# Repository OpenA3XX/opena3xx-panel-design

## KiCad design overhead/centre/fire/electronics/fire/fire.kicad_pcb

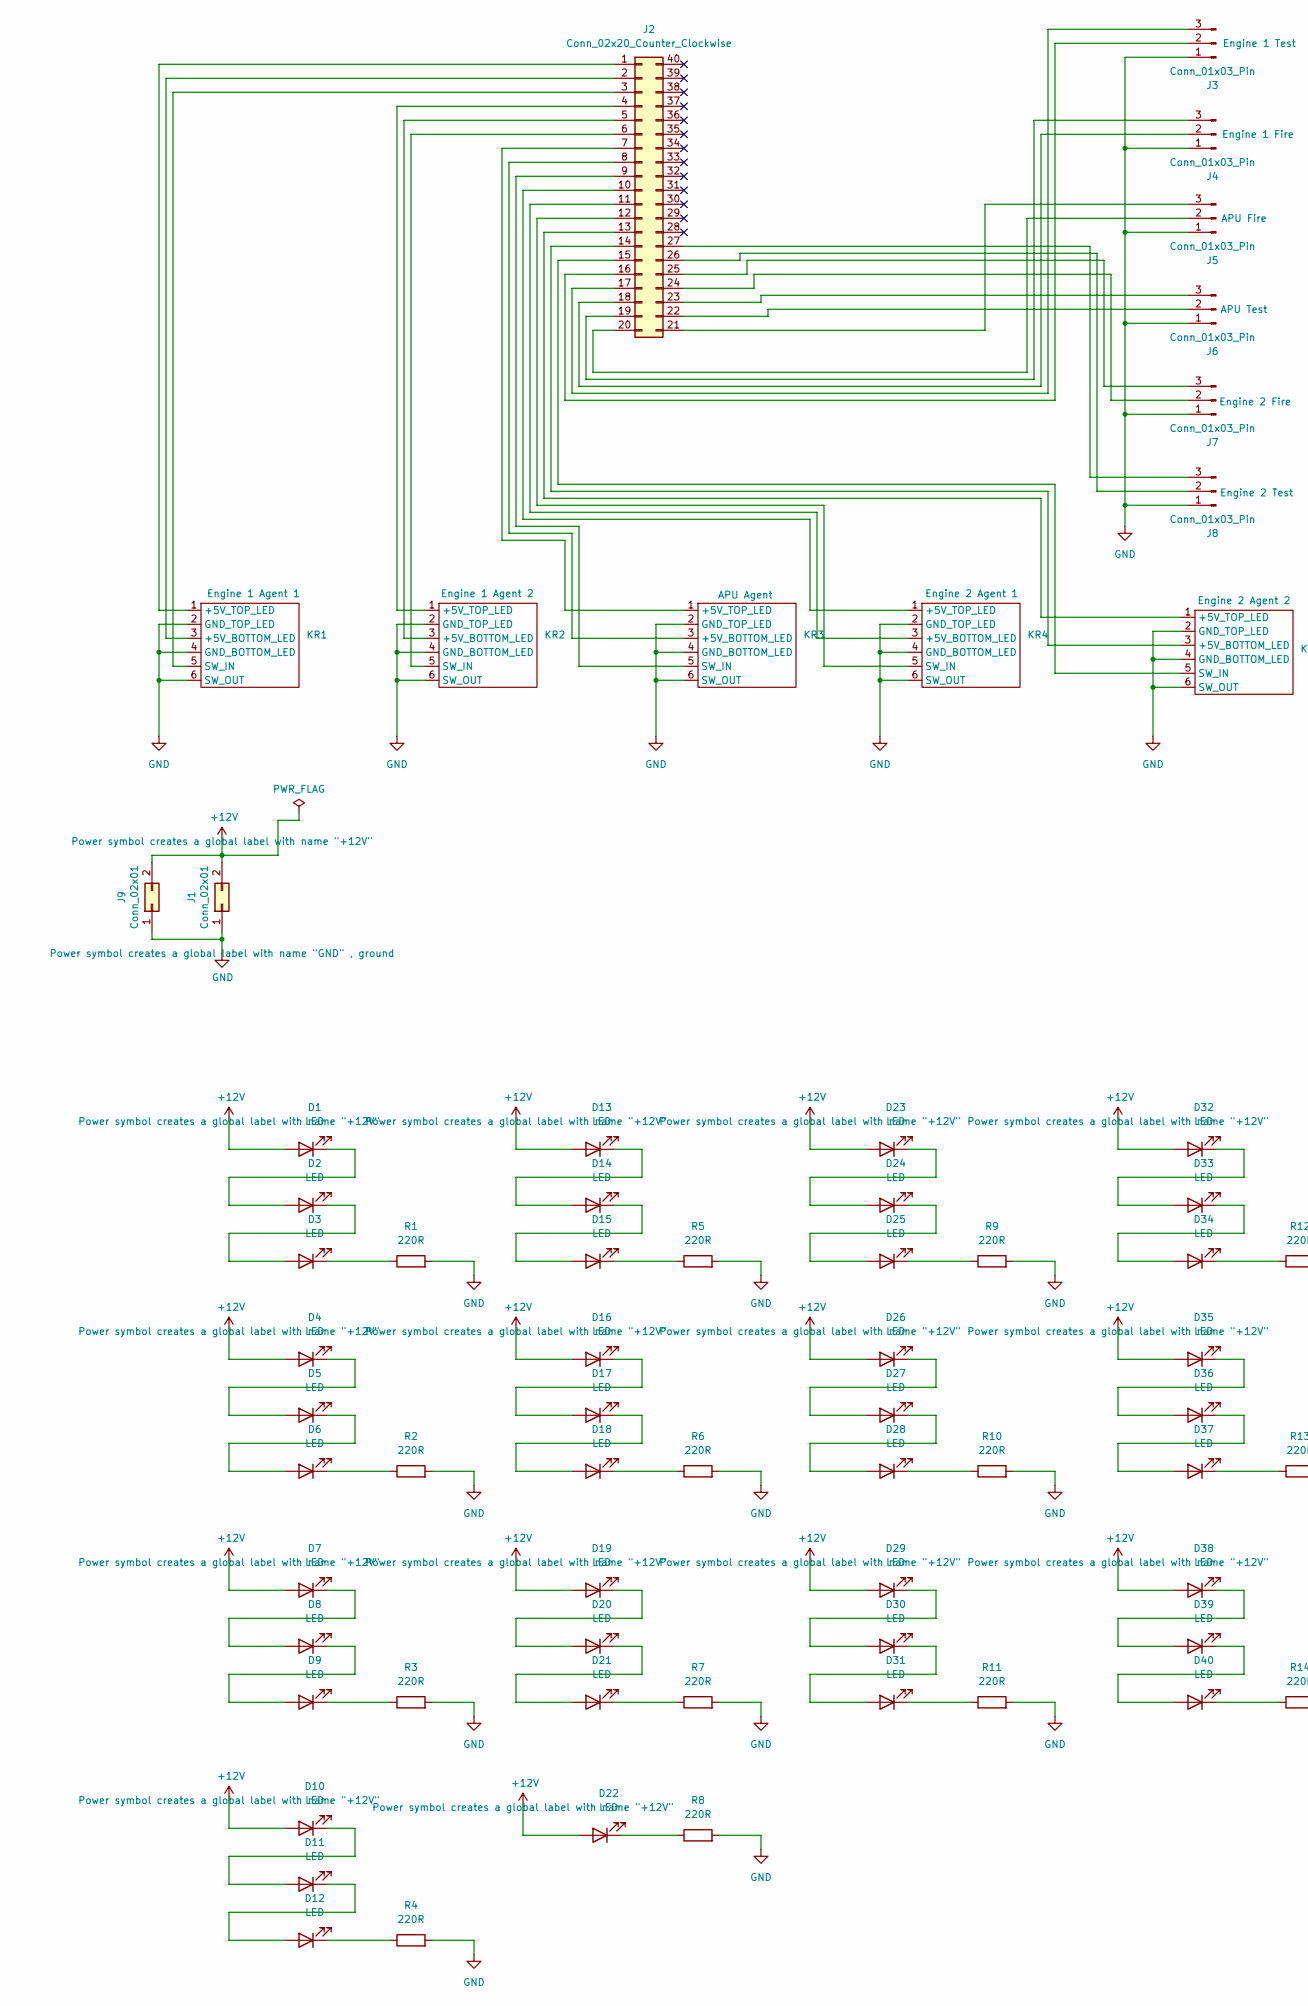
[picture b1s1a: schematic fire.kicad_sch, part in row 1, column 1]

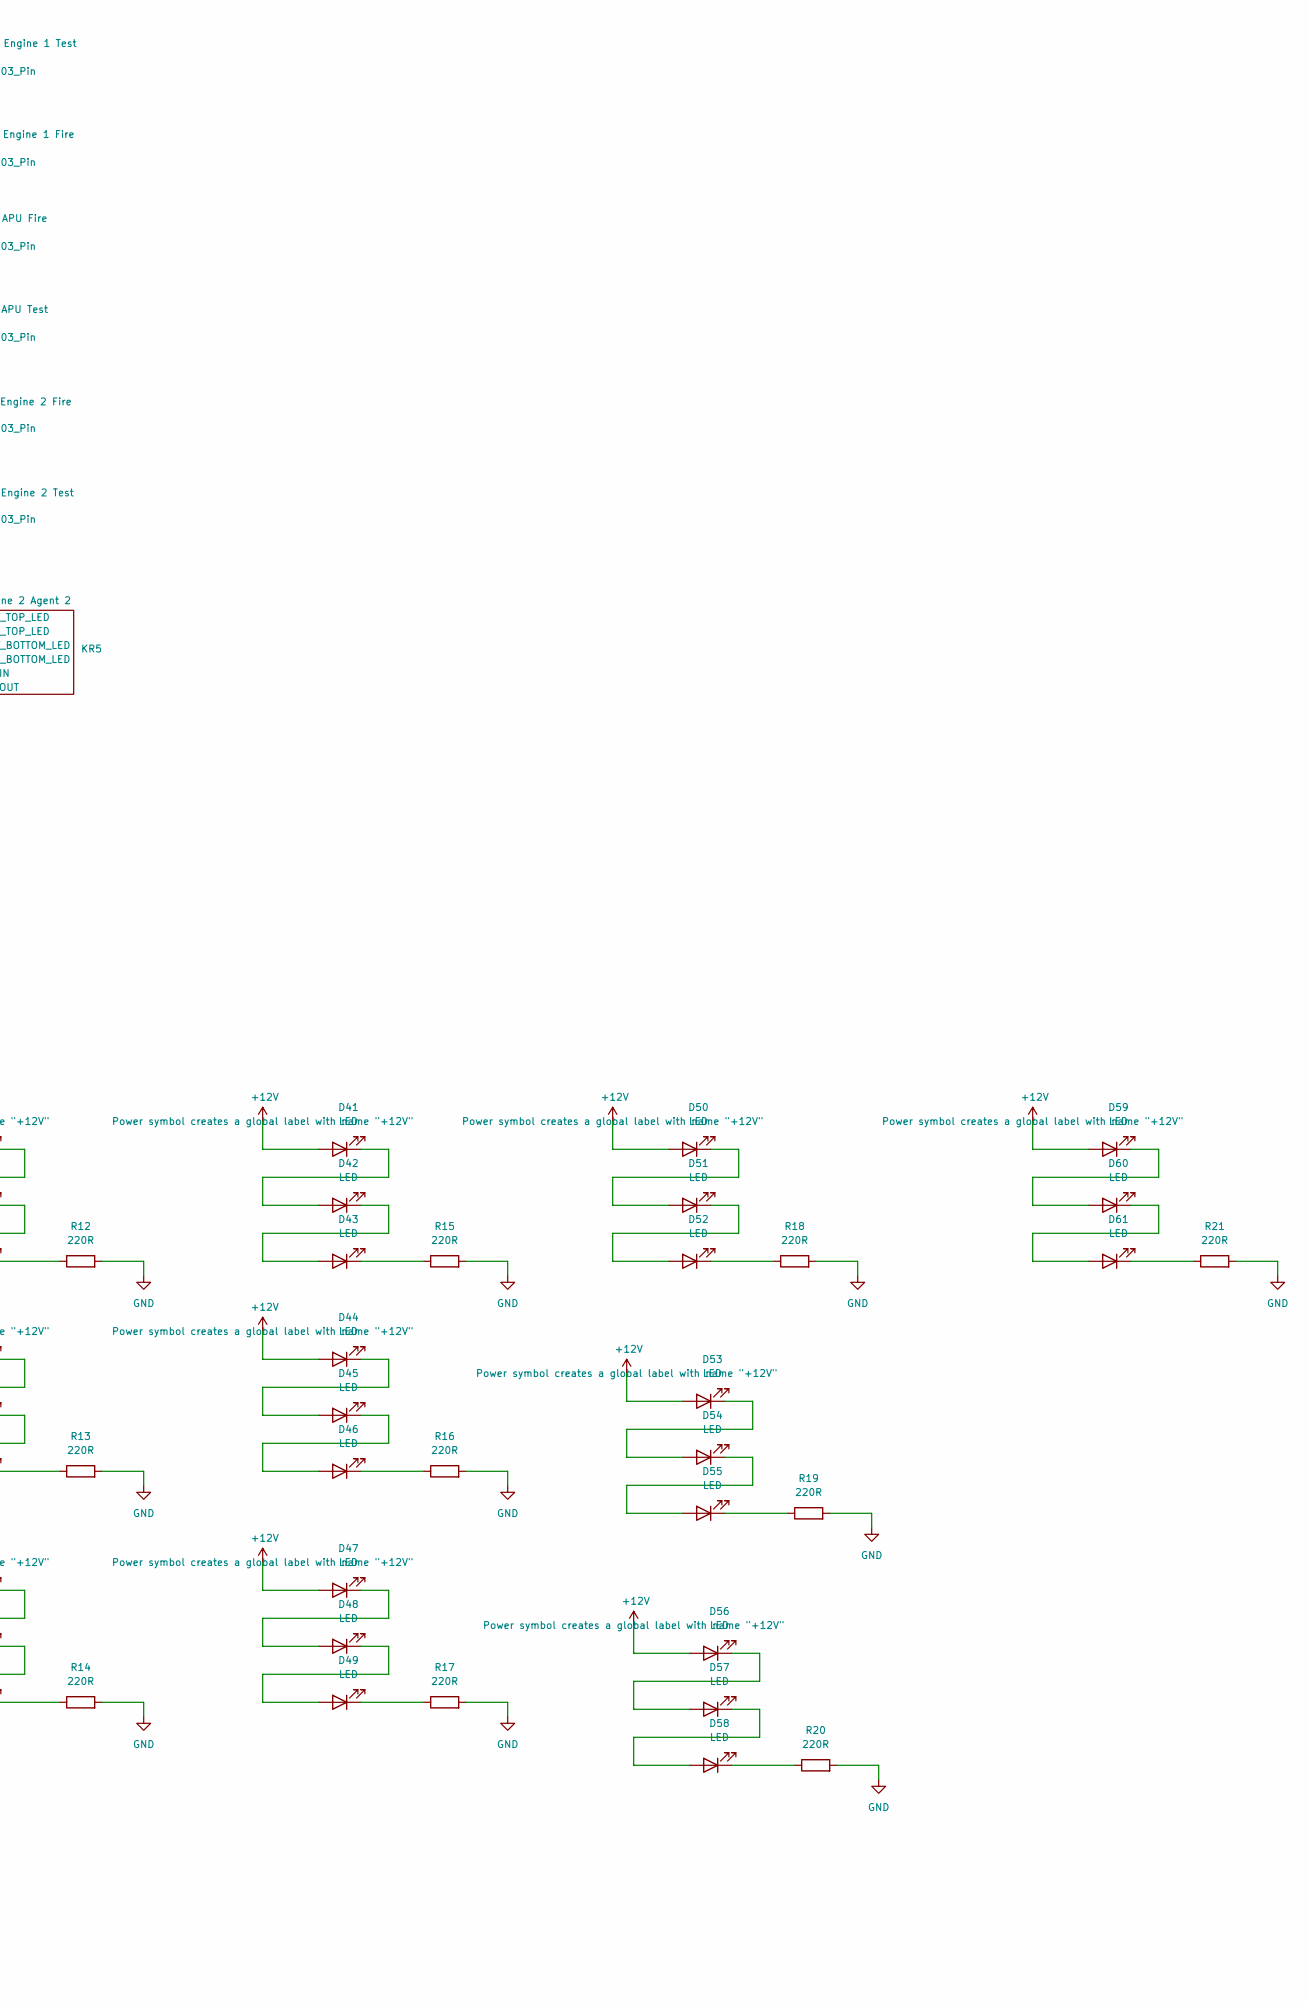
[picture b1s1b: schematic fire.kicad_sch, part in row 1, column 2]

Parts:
D1, D2, D3, D4, D5, D6, D7, D8, D9, D10, D11, D12, D13, D14, D15, D16, D17, D18, D19, D20, D21, D22, D23, D24, D25, D26, D27, D28, D29, D30, D31, D32, D33, D34, D35, D36, D37, D38, D39, D40, D41, D42, D43, D44, D45, D46, D47, D48, D49, D50, D51, D52, D53, D54, D55, D56, D57, D58, D59, D60, D61: LED; LED_Everlight-SMD3528_3.5x2.8mm_67-21ST
J1, J9: Conn_02x01; TerminalBlock_bornier-2_P5.08mm
J2: Conn_02x20_Counter_Clockwise; PinHeader_2x20_P2.54mm_Vertical
J3, J4, J5, J6, J7, J8: Conn_01x03_Pin; PinHeader_1x03_P2.54mm_Vertical
KR1, KR2, KR3, KR4, KR5: Korry Switch
R1, R2, R3, R4, R5, R6, R7, R8, R9, R10, R11, R12, R13, R14, R15, R16, R17, R18, R19, R20, R21: 220R; R_1206_3216Metric_Pad1.30x1.75mm_HandSolder

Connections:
+12V: D1.2 (A), D4.2 (A), D7.2 (A), D10.2 (A), D13.2 (A), D16.2 (A), D19.2 (A), D22.2 (A), D23.2 (A), D26.2 (A), D29.2 (A), D32.2 (A), D35.2 (A), D38.2 (A), D41.2 (A), D44.2 (A), D47.2 (A), D50.2 (A), D53.2 (A), D56.2 (A), D59.2 (A), J1.2, J9.2
GND: J1.1, J3.1, J4.1, J5.1, J6.1, J7.1, J8.1, J9.1, KR1.2 (GND_TOP_LED), KR1.4 (GND_BOTTOM_LED), KR1.6 (SW_OUT), KR2.2 (GND_TOP_LED), KR2.4 (GND_BOTTOM_LED), KR2.6 (SW_OUT), KR3.2 (GND_TOP_LED), KR3.4 (GND_BOTTOM_LED), KR3.6 (SW_OUT), KR4.2 (GND_TOP_LED), KR4.4 (GND_BOTTOM_LED), KR4.6 (SW_OUT), KR5.2 (GND_TOP_LED), KR5.4 (GND_BOTTOM_LED), KR5.6 (SW_OUT), R1.2, R2.2, R3.2, R4.2, R5.2, R6.2, R7.2, R8.2, R9.2, R10.2, R11.2, R12.2, R13.2, R14.2, R15.2, R16.2, R17.2, R18.2, R19.2, R20.2, R21.2
unnamed: D1.1 (K), D2.2 (A)
unnamed: D2.1 (K), D3.2 (A)
unnamed: D3.1 (K), R1.1
unnamed: D4.1 (K), D5.2 (A)
unnamed: D5.1 (K), D6.2 (A)
unnamed: D6.1 (K), R2.1
unnamed: D7.1 (K), D8.2 (A)
unnamed: D8.1 (K), D9.2 (A)
unnamed: D9.1 (K), R3.1
unnamed: D10.1 (K), D11.2 (A)
unnamed: D11.1 (K), D12.2 (A)
unnamed: D12.1 (K), R4.1
unnamed: D13.1 (K), D14.2 (A)
unnamed: D14.1 (K), D15.2 (A)
unnamed: D15.1 (K), R5.1
unnamed: D16.1 (K), D17.2 (A)
unnamed: D17.1 (K), D18.2 (A)
unnamed: D18.1 (K), R6.1
unnamed: D19.1 (K), D20.2 (A)
unnamed: D20.1 (K), D21.2 (A)
unnamed: D21.1 (K), R7.1
unnamed: D22.1 (K), R8.1
unnamed: D23.1 (K), D24.2 (A)
unnamed: D24.1 (K), D25.2 (A)
unnamed: D25.1 (K), R9.1
unnamed: D26.1 (K), D27.2 (A)
unnamed: D27.1 (K), D28.2 (A)
unnamed: D28.1 (K), R10.1
unnamed: D29.1 (K), D30.2 (A)
unnamed: D30.1 (K), D31.2 (A)
unnamed: D31.1 (K), R11.1
unnamed: D32.1 (K), D33.2 (A)
unnamed: D33.1 (K), D34.2 (A)
unnamed: D34.1 (K), R12.1
unnamed: D35.1 (K), D36.2 (A)
unnamed: D36.1 (K), D37.2 (A)
unnamed: D37.1 (K), R13.1
unnamed: D38.1 (K), D39.2 (A)
unnamed: D39.1 (K), D40.2 (A)
unnamed: D40.1 (K), R14.1
unnamed: D41.1 (K), D42.2 (A)
unnamed: D42.1 (K), D43.2 (A)
unnamed: D43.1 (K), R15.1
unnamed: D44.1 (K), D45.2 (A)
unnamed: D45.1 (K), D46.2 (A)
unnamed: D46.1 (K), R16.1
unnamed: D47.1 (K), D48.2 (A)
unnamed: D48.1 (K), D49.2 (A)
unnamed: D49.1 (K), R17.1
unnamed: D50.1 (K), D51.2 (A)
unnamed: D51.1 (K), D52.2 (A)
unnamed: D52.1 (K), R18.1
unnamed: D53.1 (K), D54.2 (A)
unnamed: D54.1 (K), D55.2 (A)
unnamed: D55.1 (K), R19.1
unnamed: D56.1 (K), D57.2 (A)
unnamed: D57.1 (K), D58.2 (A)
unnamed: D58.1 (K), R20.1
unnamed: D59.1 (K), D60.2 (A)
unnamed: D60.1 (K), D61.2 (A)
unnamed: D61.1 (K), R21.1
unnamed: J2.1, KR1.1 (+5V_TOP_LED)
unnamed: J2.2, KR1.3 (+5V_BOTTOM_LED)
unnamed: J2.3, KR1.5 (SW_IN)
unnamed: J2.4, KR2.1 (+5V_TOP_LED)
unnamed: J2.5, KR2.3 (+5V_BOTTOM_LED)
unnamed: J2.6, KR2.5 (SW_IN)
unnamed: J2.7, KR3.1 (+5V_TOP_LED)
unnamed: J2.8, KR3.3 (+5V_BOTTOM_LED)
unnamed: J2.9, KR3.5 (SW_IN)
unnamed: J2.10, KR4.1 (+5V_TOP_LED)
unnamed: J2.11, KR4.3 (+5V_BOTTOM_LED)
unnamed: J2.12, KR4.5 (SW_IN)
unnamed: J2.13, KR5.1 (+5V_TOP_LED)
unnamed: J2.14, KR5.3 (+5V_BOTTOM_LED)
unnamed: J2.15, KR5.5 (SW_IN)
unnamed: J2.16, J3.2
unnamed: J2.17, J3.3
unnamed: J2.18, J4.2
unnamed: J2.19, J4.3
unnamed: J2.20, J5.2
unnamed: J2.21, J5.3
unnamed: J2.22, J6.2
unnamed: J2.23, J6.3
unnamed: J2.24, J7.2
unnamed: J2.25, J7.3
unnamed: J2.26, J8.2
unnamed: J2.27, J8.3

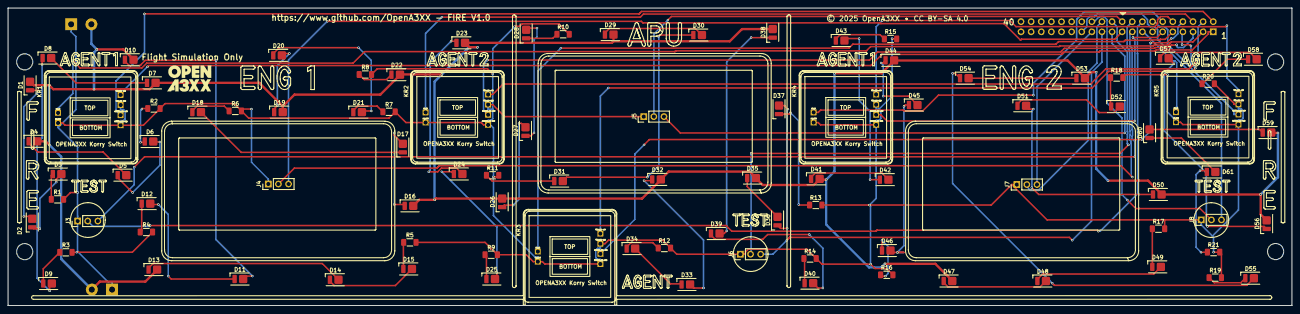
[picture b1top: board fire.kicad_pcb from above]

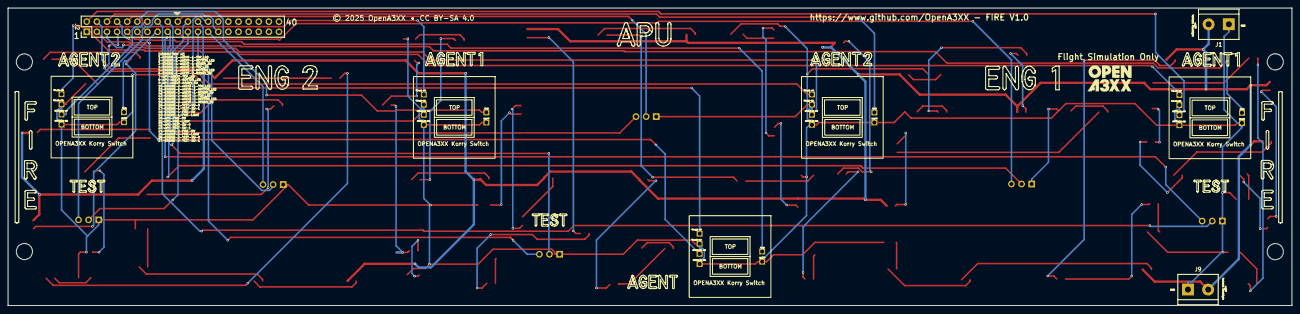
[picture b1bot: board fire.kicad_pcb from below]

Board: 2 copper layers, 322.3 x 74.7 mm, 98 parts (4 on the bottom side), 90 nets.

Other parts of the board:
bottom: LOGO; OpenA3XXLogoSmall
top: LOGO; OpenA3XXLogoSmall

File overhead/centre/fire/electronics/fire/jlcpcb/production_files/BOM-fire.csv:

Comment,Designator,Footprint,LCSC,Quantity
LED,"D1,D10,D11,D12,D13,D14,D15,D16,D17,D18,D19,D2,D20,D21,D22,D23,D24,D25,D26,D27,D28,D29,D3,D30,D31,D32,D33,D34,D35,D36,D37,D38,D39,D4,D40,D41,D42,D43,D44,D45,D46,D47,D48,D49,D5,D50,D51,D52,D53,D54,D55,D56,D57,D58,D59,D6,D60,D61,D7,D8,D9",LED_Everlight-SMD3528_3.5x2.8mm_67-21ST,C2843803,61
220R,"R1,R10,R11,R12,R13,R14,R15,R16,R17,R18,R19,R2,R20,R21,R3,R4,R5,R6,R7,R8,R9",R_1206_3216Metric_Pad1.30x1.75mm_HandSolder,C2933785,21
Conn_01x03_Pin,"J3,J4,J5,J6,J7,J8",PinHeader_1x03_P2.54mm_Vertical,C2937625,6
Conn_02x01,"J1,J9",TerminalBlock_bornier-2_P5.08mm,C592976,2
Conn_02x20_Counter_Clockwise,J2,PinHeader_2x20_P2.54mm_Vertical,C725892,1
~,KR4,Korry Switch,,1
~,KR1,Korry Switch,,1
~,KR5,Korry Switch,,1
~,KR2,Korry Switch,,1
~,KR3,Korry Switch,,1

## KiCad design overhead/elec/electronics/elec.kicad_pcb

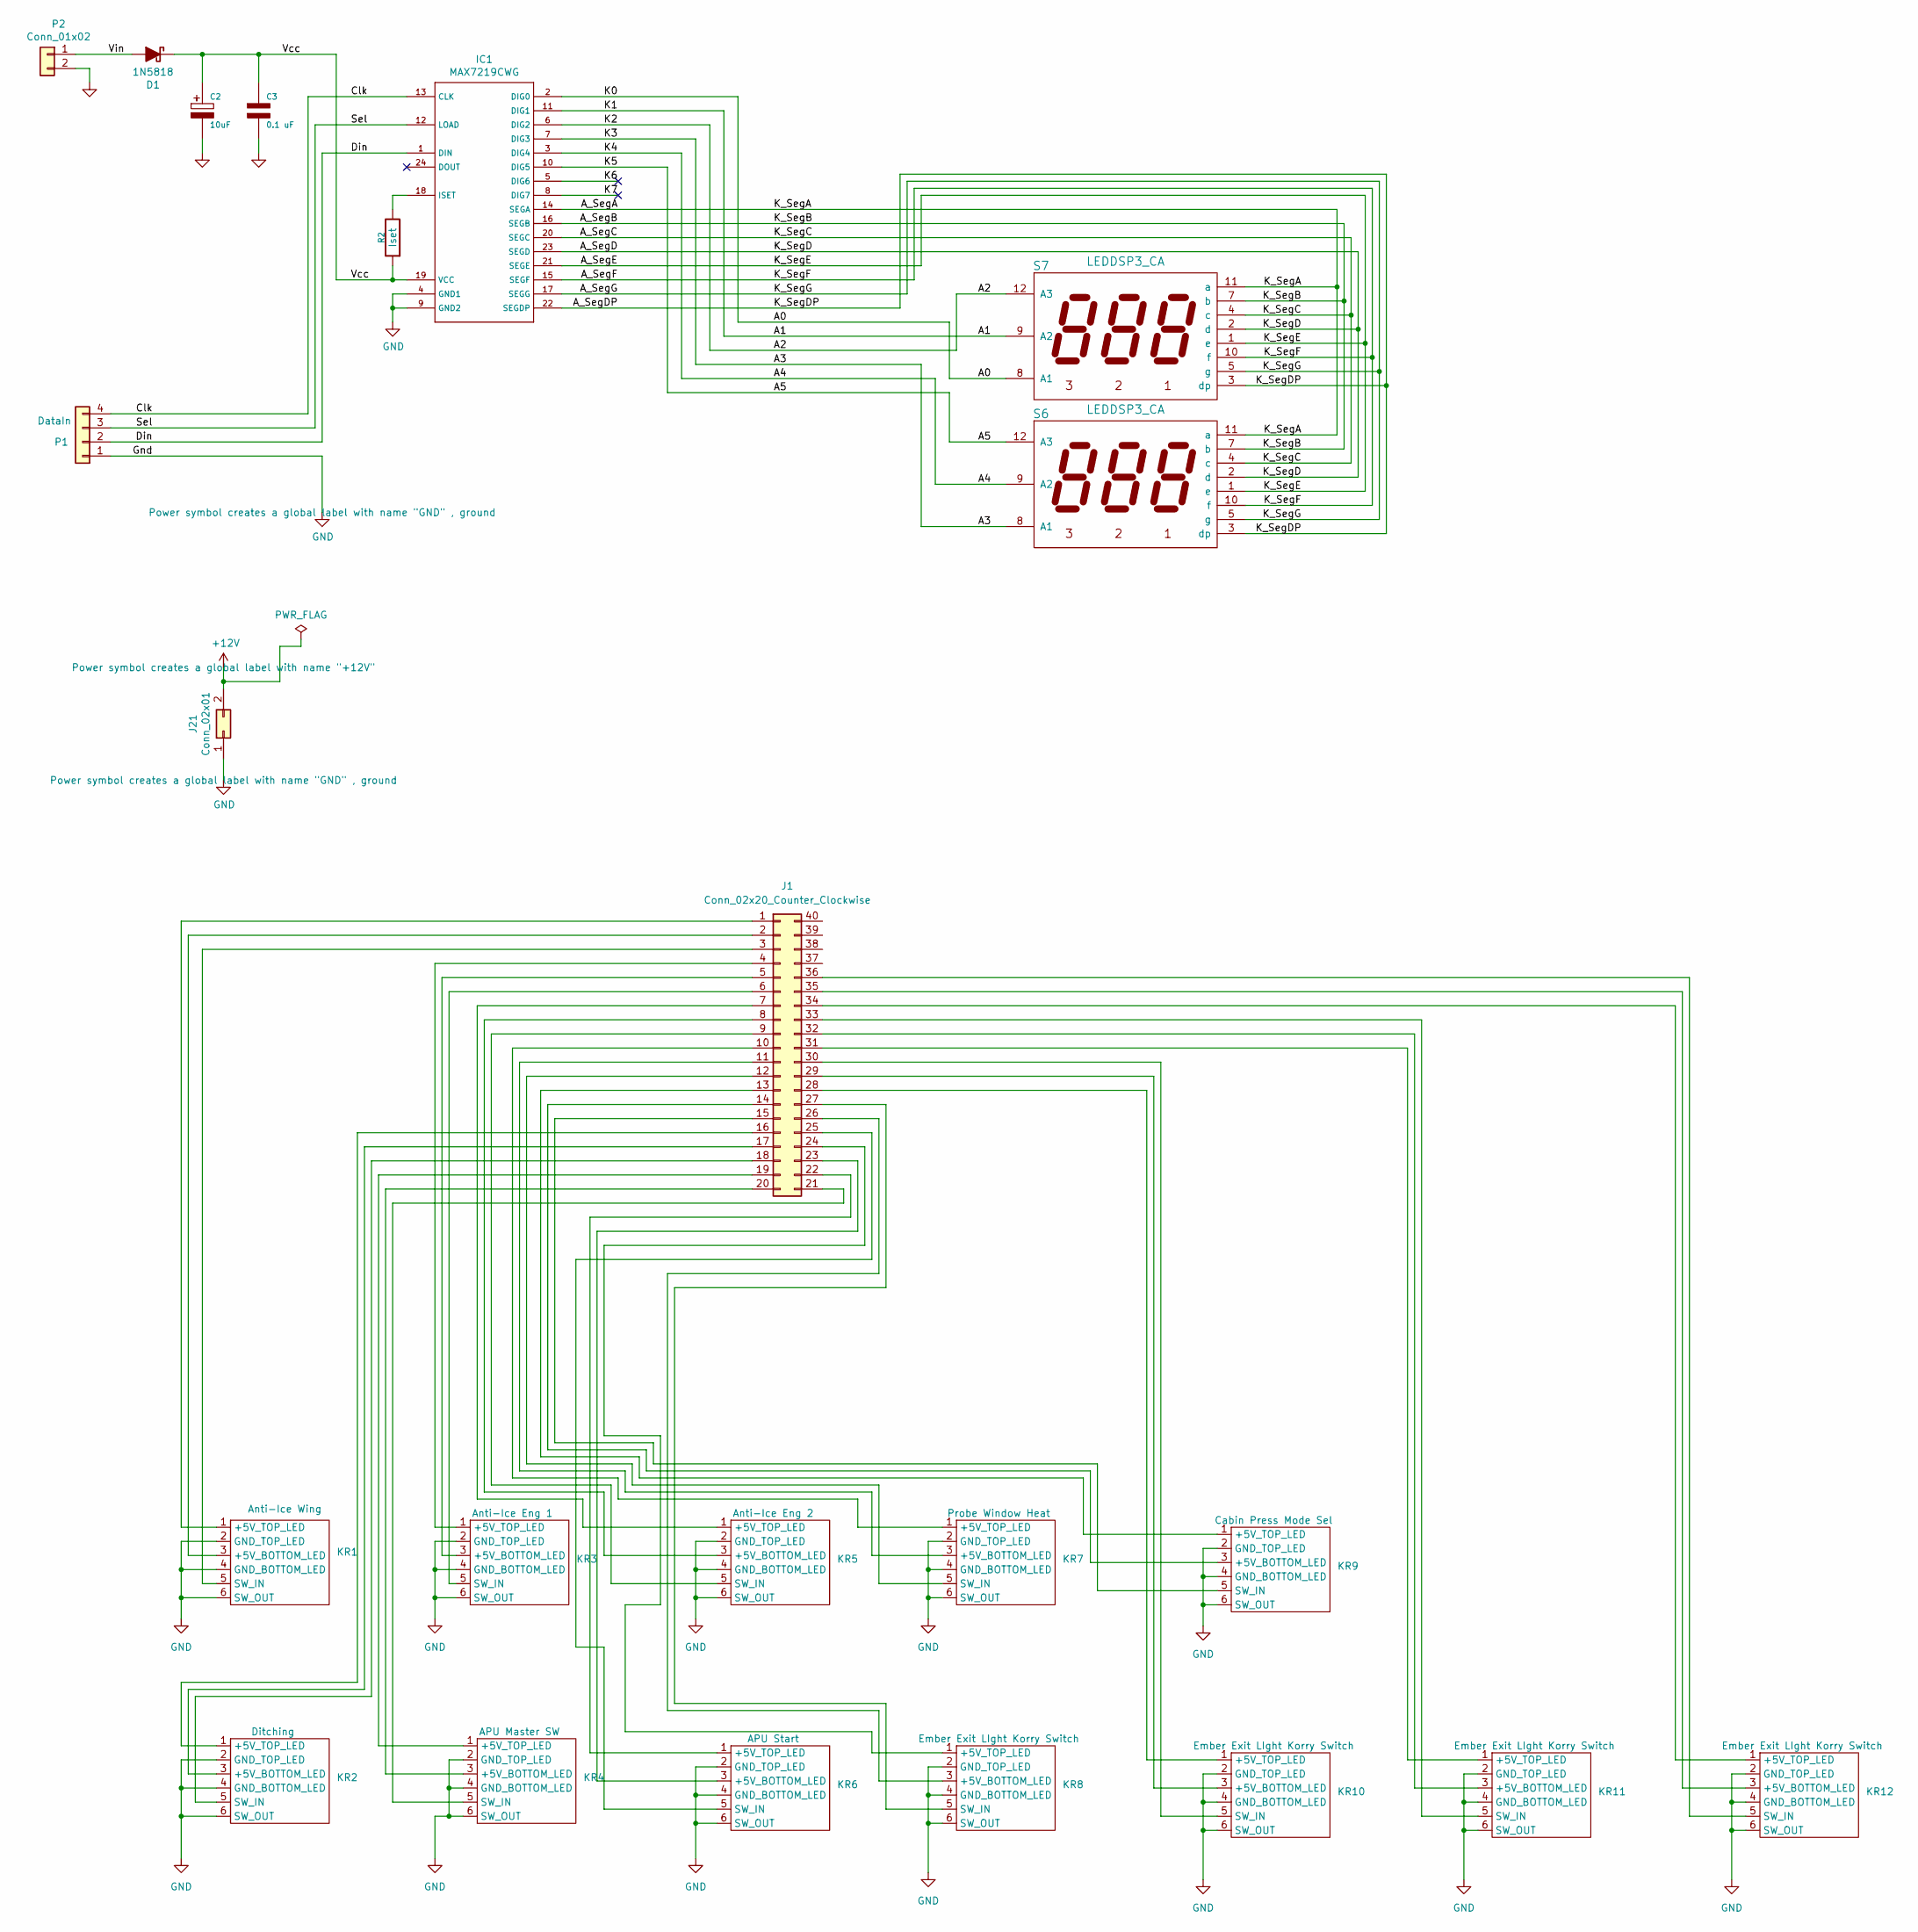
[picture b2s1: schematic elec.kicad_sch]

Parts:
C2: 10uF; CP_Radial_D5.0mm_P2.50mm
C3: 0.1 uF; C_1206_3216Metric_Pad1.33x1.80mm_HandSolder
D1: 1N5818; D_SMA_Handsoldering
IC1: MAX7219CWG; SOIC-24W_7.5x15.4mm_P1.27mm
J1: Conn_02x20_Counter_Clockwise; PinHeader_2x20_P2.54mm_Vertical
J21: Conn_02x01; TerminalBlock_bornier-2_P5.08mm
KR1, KR2, KR3, KR4, KR5, KR6, KR7, KR8, KR9, KR10, KR11, KR12: Korry Switch
P1: DataIn; PinHeader_1x04_P2.54mm_Vertical
P2: Conn_01x02; TerminalBlock_bornier-2_P5.08mm
R2: Iset; R_Axial_DIN0207_L6.3mm_D2.5mm_P10.16mm_Horizontal
S6, S7: LEDDSP3_CA; Disp7s3x_036

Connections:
+12V: J21.2
/A0: IC1.2 (DIG0), S7.8 (A1)
/A1: IC1.11 (DIG1), S7.9 (A2)
/A2: IC1.6 (DIG2), S7.12 (A3)
/A3: IC1.7 (DIG3), S6.8 (A1)
/A4: IC1.3 (DIG4), S6.9 (A2)
/A5: IC1.10 (DIG5), S6.12 (A3)
/A_SegA: IC1.14 (SEGA), S6.11 (a), S7.11 (a)
/A_SegB: IC1.16 (SEGB), S6.7 (b), S7.7 (b)
/A_SegC: IC1.20 (SEGC), S6.4 (c), S7.4 (c)
/A_SegD: IC1.23 (SEGD), S6.2 (d), S7.2 (d)
/A_SegDP: IC1.22 (SEGDP), S6.3 (dp), S7.3 (dp)
/A_SegE: IC1.21 (SEGE), S6.1 (e), S7.1 (e)
/A_SegF: IC1.15 (SEGF), S6.10 (f), S7.10 (f)
/A_SegG: IC1.17 (SEGG), S6.5 (g), S7.5 (g)
/Clk: IC1.13 (CLK), P1.4
/Din: IC1.1 (DIN), P1.2
/K6: IC1.5 (DIG6)
/K7: IC1.8 (DIG7)
/Sel: IC1.12 (LOAD), P1.3
/Vcc: C2.1, C3.1, D1.1 (K), IC1.19 (VCC), R2.1
/Vin: D1.2 (A), P2.1
GND: C2.2, C3.2, IC1.4 (GND1), IC1.9 (GND2), J21.1, KR1.2 (GND_TOP_LED), KR1.4 (GND_BOTTOM_LED), KR1.6 (SW_OUT), KR2.2 (GND_TOP_LED), KR2.4 (GND_BOTTOM_LED), KR2.6 (SW_OUT), KR3.2 (GND_TOP_LED), KR3.4 (GND_BOTTOM_LED), KR3.6 (SW_OUT), KR4.2 (GND_TOP_LED), KR4.4 (GND_BOTTOM_LED), KR4.6 (SW_OUT), KR5.2 (GND_TOP_LED), KR5.4 (GND_BOTTOM_LED), KR5.6 (SW_OUT), KR6.2 (GND_TOP_LED), KR6.4 (GND_BOTTOM_LED), KR6.6 (SW_OUT), KR7.2 (GND_TOP_LED), KR7.4 (GND_BOTTOM_LED), KR7.6 (SW_OUT), KR8.2 (GND_TOP_LED), KR8.4 (GND_BOTTOM_LED), KR8.6 (SW_OUT), KR9.2 (GND_TOP_LED), KR9.4 (GND_BOTTOM_LED), KR9.6 (SW_OUT), KR10.2 (GND_TOP_LED), KR10.4 (GND_BOTTOM_LED), KR10.6 (SW_OUT), KR11.2 (GND_TOP_LED), KR11.4 (GND_BOTTOM_LED), KR11.6 (SW_OUT), KR12.2 (GND_TOP_LED), KR12.4 (GND_BOTTOM_LED), KR12.6 (SW_OUT), P1.1, P2.2
unnamed: IC1.18 (ISET), R2.2
unnamed: J1.1, KR1.1 (+5V_TOP_LED)
unnamed: J1.2, KR1.3 (+5V_BOTTOM_LED)
unnamed: J1.3, KR1.5 (SW_IN)
unnamed: J1.4, KR3.1 (+5V_TOP_LED)
unnamed: J1.5, KR3.3 (+5V_BOTTOM_LED)
unnamed: J1.6, KR3.5 (SW_IN)
unnamed: J1.7, KR5.1 (+5V_TOP_LED)
unnamed: J1.8, KR5.3 (+5V_BOTTOM_LED)
unnamed: J1.9, KR5.5 (SW_IN)
unnamed: J1.10, KR7.1 (+5V_TOP_LED)
unnamed: J1.11, KR7.3 (+5V_BOTTOM_LED)
unnamed: J1.12, KR7.5 (SW_IN)
unnamed: J1.13, KR9.1 (+5V_TOP_LED)
unnamed: J1.14, KR9.3 (+5V_BOTTOM_LED)
unnamed: J1.15, KR9.5 (SW_IN)
unnamed: J1.16, KR2.1 (+5V_TOP_LED)
unnamed: J1.17, KR2.3 (+5V_BOTTOM_LED)
unnamed: J1.18, KR2.5 (SW_IN)
unnamed: J1.19, KR4.1 (+5V_TOP_LED)
unnamed: J1.20, KR4.3 (+5V_BOTTOM_LED)
unnamed: J1.21, KR4.5 (SW_IN)
unnamed: J1.22, KR6.1 (+5V_TOP_LED)
unnamed: J1.23, KR6.3 (+5V_BOTTOM_LED)
unnamed: J1.24, KR8.1 (+5V_TOP_LED)
unnamed: J1.25, KR6.5 (SW_IN)
unnamed: J1.26, KR8.3 (+5V_BOTTOM_LED)
unnamed: J1.27, KR8.5 (SW_IN)
unnamed: J1.28, KR10.1 (+5V_TOP_LED)
unnamed: J1.29, KR10.3 (+5V_BOTTOM_LED)
unnamed: J1.30, KR10.5 (SW_IN)
unnamed: J1.31, KR11.1 (+5V_TOP_LED)
unnamed: J1.32, KR11.3 (+5V_BOTTOM_LED)
unnamed: J1.33, KR11.5 (SW_IN)
unnamed: J1.34, KR12.1 (+5V_TOP_LED)
unnamed: J1.35, KR12.3 (+5V_BOTTOM_LED)
unnamed: J1.36, KR12.5 (SW_IN)

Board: 2 copper layers, 25 parts (10 on the bottom side), 57 nets, no tracks yet.

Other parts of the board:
bottom: LOGO; OpenA3XXLogoSmall
top: LOGO; OpenA3XXLogoSmall

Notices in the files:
overhead/centre/fire/electronics/fire/fire.kicad_pcb:
© 2025 OpenA3XX • CC BY-SA 4.0
